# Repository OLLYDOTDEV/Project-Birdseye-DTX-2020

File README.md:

# Project-Birdseye-DTX-2020
The initial plan is to create a device that is made for the sole purpose of a Preemptive Security system for People who work with Confidential/Private Information and need to work on potentially more public places where one cant Guarantee fully secure/discrete room.    My Approach to solving this is with a wireless computing node  That Takes Sensor data from a variety of senses. Then the Data from the Senses is taken then and processed to determine whether there is a security breach if so then it will Relay that info over to the Raspberry Pi W that then Emulates an HID (Human interface device) Using the P4wnP1_aloa made by mame82 to Execute a custom user-defined action that will be set via  Apache server hosted of the Raspberry Pi W Communicating From a web interface back to the server via a web socket

 Projectbirdeye is out of the box working solution for this 
________
See for devlog of project [here](https://github.com/OLLYDOTDEV/Project-Birdseye-DTX-2020/issues?q=is%3Aissue+)

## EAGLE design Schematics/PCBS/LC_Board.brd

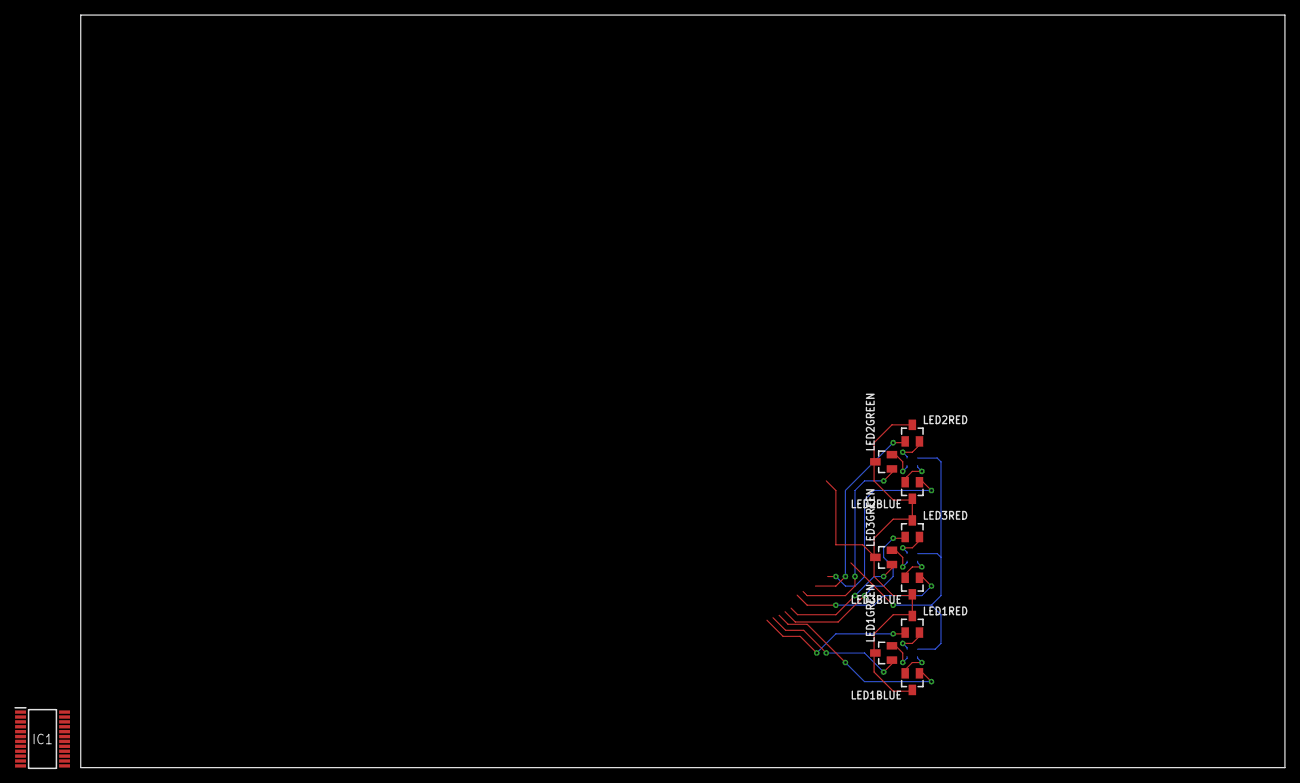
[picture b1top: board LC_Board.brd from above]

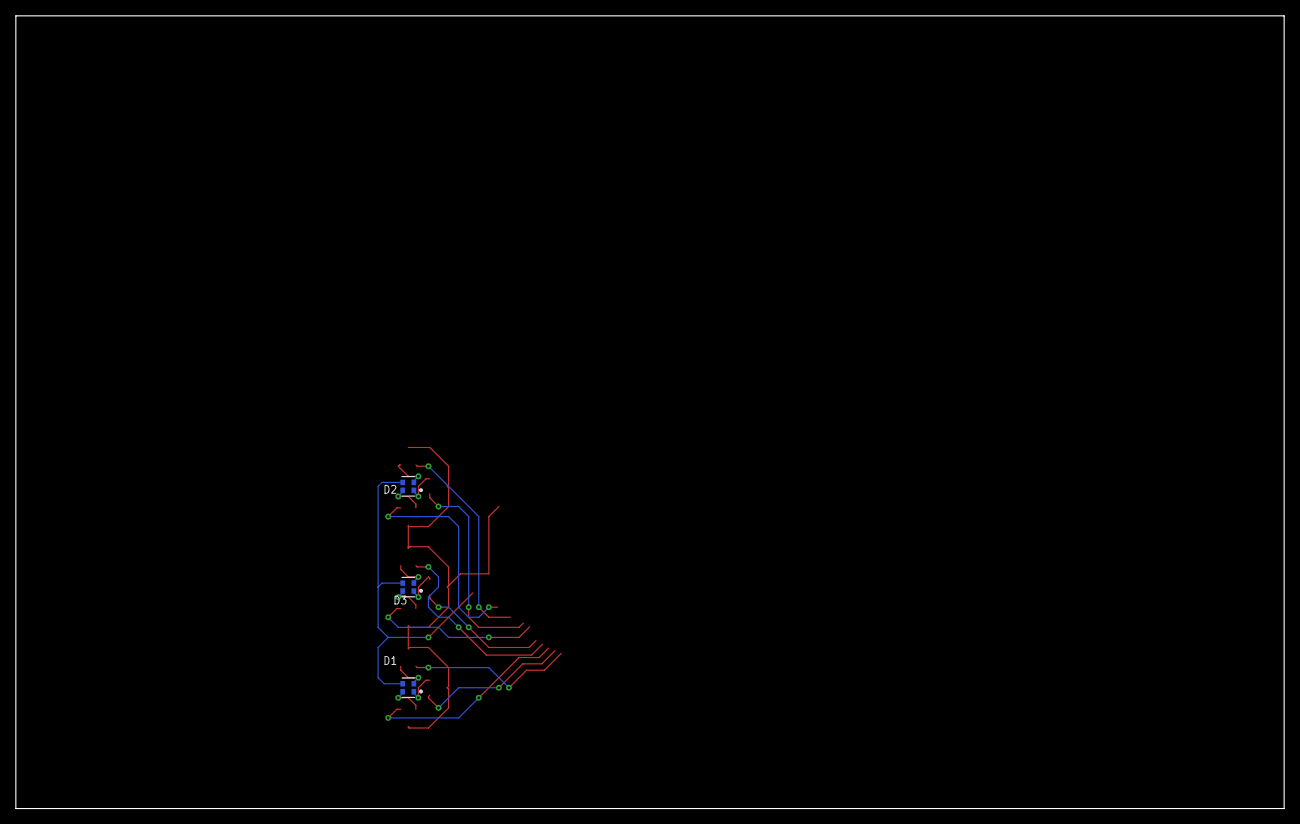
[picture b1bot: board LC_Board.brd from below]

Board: 2 copper layers, 160.0 x 100.0 mm, 13 parts (3 on the bottom side), 11 nets.

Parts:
D1, D2, D3: DIALIGHT_598-8710-307FDIALIGHT_598-8710-307F_0_0; DIALIGHT_598-8710-307F_0
IC1: STP16C596M; SOP65P638X110-24N
LED1BLUE, LED1GREEN, LED1RED, LED2BLUE, LED2GREEN, LED2RED, LED3BLUE, LED3GREEN, LED3RED: BSS138; TRANSISTOR-FET_SOT23

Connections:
3.3V_RAIL: D1.4, D2.4, D3.4
BLUE1: D1.2, LED1BLUE.2
BLUE2: D2.2, LED2BLUE.2
BLUE3: D3.2, LED3BLUE.2
GND: IC1.1, LED1BLUE.3, LED1GREEN.3, LED1RED.3, LED2BLUE.3, LED2GREEN.3, LED2RED.3, LED3BLUE.3, LED3GREEN.3, LED3RED.3
GREEN1: D1.1, LED1GREEN.2
GREEN2: D2.1, LED2GREEN.2
GREEN3: D3.1, LED3GREEN.2
RED1: D1.3, LED1RED.2
RED2: D2.3, LED2RED.2
RED3: D3.3, LED3RED.2

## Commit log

2020-01-27 test
2020-01-29 more testing
2020-02-09 Init Eagle Upload
2020-02-10 added 16mhz +grounding
2020-02-10 added need libraries
2020-02-11 working on VCC power
2020-02-11 update on gitignore
2020-02-11 added .gitignore so that the temp .s#1, .s#2 files dont get uploard to upstream git repo
2020-02-12 Start of NRF24lo1 hook up & LED’s
2020-02-12 removed LED from ROMS
2020-02-13 school day back up
2020-02-21 led + atmega328
2020-02-24 added power rail and regulator
2020-02-24 added more libraries
2020-02-25 LT1763CS8-5TRPBF.lbr and LT1763CS8-3.3_TRPBF.lbr2. Also updated Regulator in LED PCB to the correct variant
2020-02-26 update power Rail
2020-02-26 completion of Of the first implementation of the power system
2020-02-27 join Led To IC
2020-02-27 connected LED Mosfets to IC + Add headers
2020-02-27 Fix layout issues via fix to grid
2020-03-01 updated Fauly .lbr as the N channel MOSFETS has a labels on the SOT-23-3
2020-03-01 started on Bidirectional Logic Level Converter
2020-03-02 Added RXD Logic level converter && IO update
2020-03-05 updated RXD_IN 5v to 3.3v
2020-03-05 LEDs.sch -> LC_Board.sch
2020-03-05 update .gitignore && added MOSFET value to board
2020-03-05 removed old LED .sch
2020-03-08 updated IO
2020-03-08 3.3v && 5v selcetor headers added
2020-03-09 added lables to 5v to 3.3v on RXI
2020-03-09 Added lables to LC_board led gnd control mostfets
2020-03-10 PCB layout fixed
2020-03-10 added PCB .BRD file
2020-03-10 updated Reset_pull footprint to 603 from 403
2020-03-10 routing for PCB 1 ok outcome
2020-03-12 LC_board PCB pos nearing finish for R1
2020-03-13 back up be for remixing LED pos
2020-03-13 Syncing schematic with board fixed
2020-03-15 weekend backup
2020-03-15 R1 Finish (yet to test)
2020-06-17 added Schematics/libraries/STP16C596M.lbr
2020-06-17 updated LC_Board IO to match need pins for Shift registers
2020-06-20 added voltage divider and input pins Shift Register
2020-06-22 connected LED & IO to Shift register
2020-06-28 added header pins for IR Sensor
2020-07-07 V1 of IR Read
2020-07-18 PIR sensor test
2020-07-19 Full Trigger test part started with just base PIR code
2020-07-22 Smoothing class test ERROR
2020-07-22 class for smoothing in progress
2020-07-23 class smoothing untested
2020-07-23 smoothing data convetion to class working and tested
2020-07-23 FUll Sensor test working with boot info error
2020-07-23 change starting _total variable value
2020-07-24 fixed load value error
2020-07-24 fixed false alert when in boot with temp return value
2020-07-24 input data count working = IR sensor full working
2020-07-28 added missing LED PCB link
2020-07-29 added volage divider for NRF24
2020-08-02 NRF24
2020-08-03 connected NRF24 to ATMEGA328p
2020-08-10 added *3 AA battery holder and battery holder .lbr
2020-08-14 Add .whitesource configuration file
2020-08-19 setup for RX|TX wireless code
2020-08-20 Added unsentdata logic
2020-08-20 TX mode completed but not tested
2020-08-21 base RX function (untested)
2020-08-23 small change to TX while loop
2020-08-25 fixed Syntax
2020-08-26 tidied up directory
2020-08-26 .ino file for fulling channel with data to be read (for debugging)
2020-08-26 added Bulk Read & Updated Bulk send
2020-08-27 Working DIY Send and Receive
2020-08-27 refracted code and smoothed out functionality
2020-08-28 receiving compatibility within BULK and speed / functionality enhancements
2020-08-29 NRF24 LIB update.
2020-08-29 ADDED ACK
2020-08-30 started implementing radio transmitting waiting for available transmission slot
2020-08-30 added Aluminum Electrolytic Capacitor for stabilizing power
2020-08-30 tidied up repo
2020-08-31 v2 of added radio down state in transmission (untested)
2020-08-31 work TX standdown subsystem implemented and tested
2020-08-31 fixed spelling
2020-08-31 fixed subsystem TX down override
2020-08-31 reflected code for functionality
2020-09-01 added get size of payloads with Sizeof()
2020-09-02 Added String to Char Test file
2020-09-03 optimisations
2020-09-03 Radio Test of String > Char array > String
2020-09-04 added border case protection error checking
2020-09-04 added custom data structures + border case packet protection
2020-09-07 added compiler files
2020-09-08 changed folder structure & added .cpp file equivalence to run on RPI
2020-09-08 updated to ignore .vscode config folder
2020-09-08 refracted
2020-09-09 changed folder name
2020-09-09 Improvements to Wireless data processing
2020-09-09 RPI sch
2020-09-09 change file structure
2020-09-09 added packet checking
2020-09-10 added header and mode switch
2020-09-10 added Wireless data processing (not tested yet)
2020-09-10 updated switch cases
2020-09-14 parse command line parameters test
2020-09-14 changed logic to for loop
2020-09-14 AUG Parsing
2020-09-15 change file layout
2020-09-15 makefile rearrangement
2020-09-15 debuged with just toupper to fix
2020-09-15 Segmentation fault
2020-09-15 main() fix
2020-09-17 fixed compile error:Transmitting...RF24 HARDWARE FAIL: Radio not responding, verify pin connections, wiring, etc.
2020-09-18 work update
2020-09-19 webserver interface start
2020-09-20 added working web interface
2020-09-20 RPI makefile
2020-09-21 sensor control added
2020-09-21 Updated communication procress
2020-09-21 increase reliability of page refresh system
2020-09-21 sensor mode enable|disable added and working (tested)
2020-09-22 HID test (lock screen)
2020-09-22 added more HID scripts
2020-09-22 optimise code by reducing the amount of unneeded transmissions
2020-09-22 configured hid activation to only activate once per trigger
2020-09-22 Updated README.md to increase accuracy of data
2020-09-23 added more HID test scripts
2020-09-23 changed file name
2020-09-23 changed to allow better dynamic control over HID scripts
2020-09-23 updated perms | added cp
2020-09-23 file upload and Control panel complete
2020-09-23 Create LICENSE
    privacy and licensing
2020-09-23 fixed scripts not executing
2020-09-23 allow headless tranmisstion
2020-09-23 fixed OFF signal not being sent
2020-09-24 changed something
2020-10-19 NCEA Docs
